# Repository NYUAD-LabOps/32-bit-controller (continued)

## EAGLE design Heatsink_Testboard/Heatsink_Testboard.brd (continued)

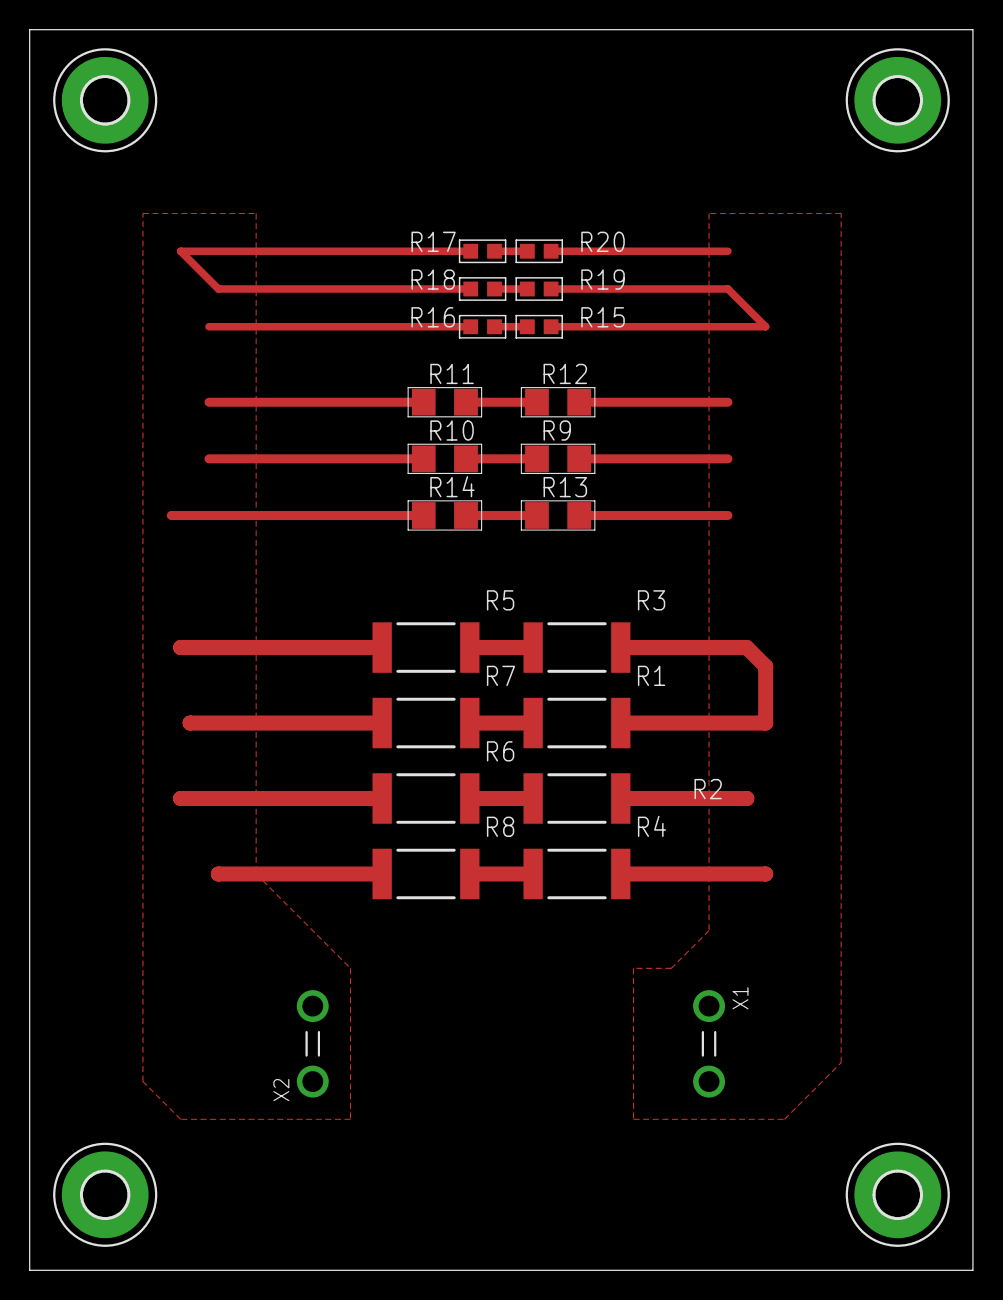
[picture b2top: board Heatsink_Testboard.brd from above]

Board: 2 copper layers, 63.5 x 83.5 mm, 26 parts (0 on the bottom side), 12 nets.

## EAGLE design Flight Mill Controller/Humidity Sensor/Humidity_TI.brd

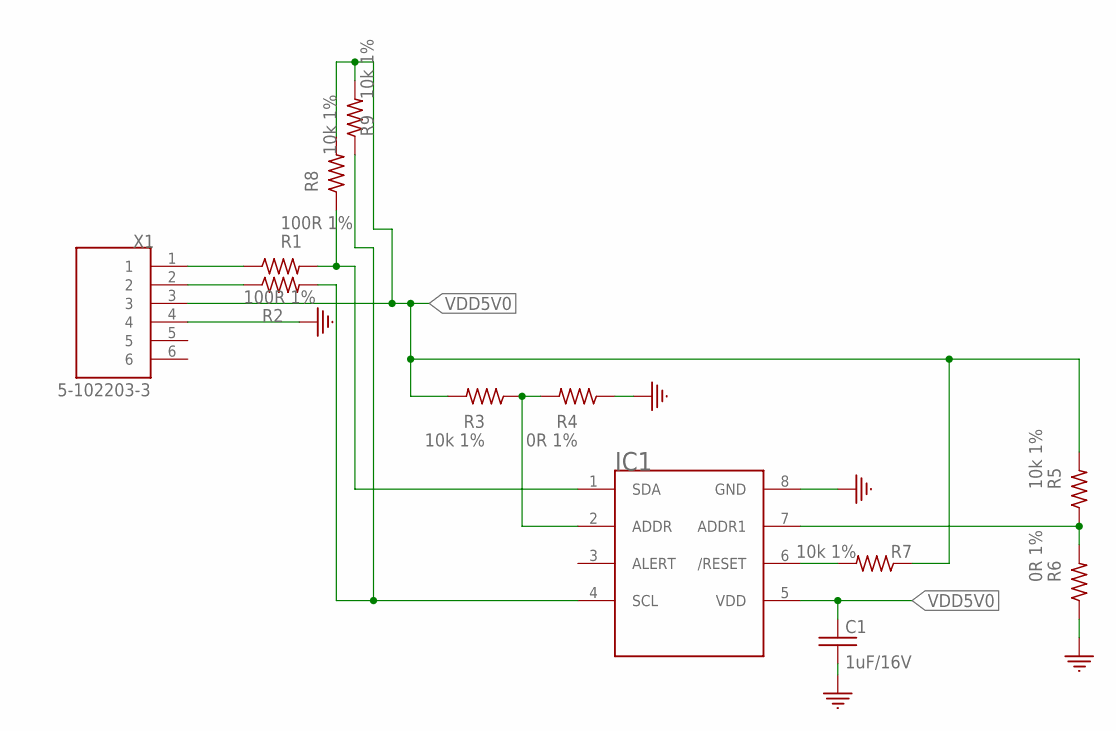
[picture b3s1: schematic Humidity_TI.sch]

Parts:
C1: 1uF/16V; EIA0603
IC1: HDC3021-Q1; WSON8
R1, R2: 100R 1%; EIA0603
R3, R5, R7, R8, R9: 10k 1%; EIA0603
R4, R6: 0R 1%; EIA0603
X1: 5-102203-3; TE_5-102203-3

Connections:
GND: C1.2, IC1.8 (GND), R4.1, R6.1, X1.4
unnamed: R1.1, X1.1
unnamed: IC1.1 (SDA), R1.2, R8.1
unnamed: IC1.4 (SCL), R2.2, R9.1
unnamed: R2.1, X1.2
unnamed: IC1.2 (ADDR), R3.1, R4.2
unnamed: IC1.7 (ADDR1), R5.1, R6.2
unnamed: IC1.6 (/RESET), R7.2
VDD5V0: C1.1, IC1.5 (VDD), R3.2, R5.2, R7.1, R8.2, R9.2, X1.3

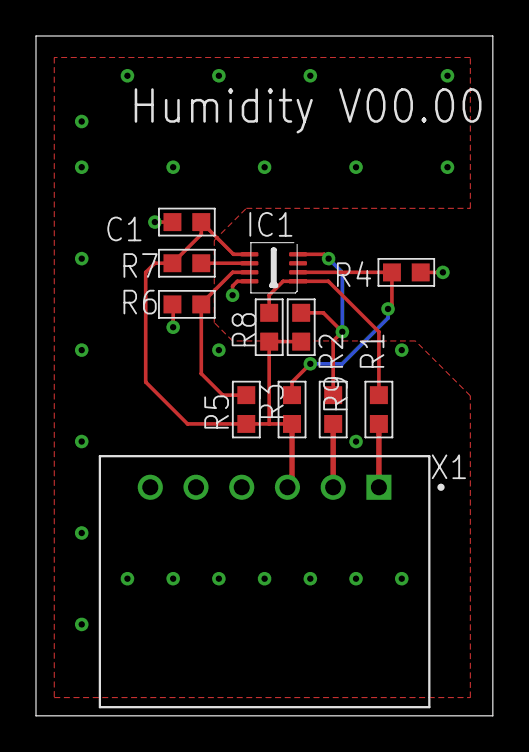
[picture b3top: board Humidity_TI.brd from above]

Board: 2 copper layers, 25.4 x 37.8 mm, 12 parts (0 on the bottom side), 9 nets.

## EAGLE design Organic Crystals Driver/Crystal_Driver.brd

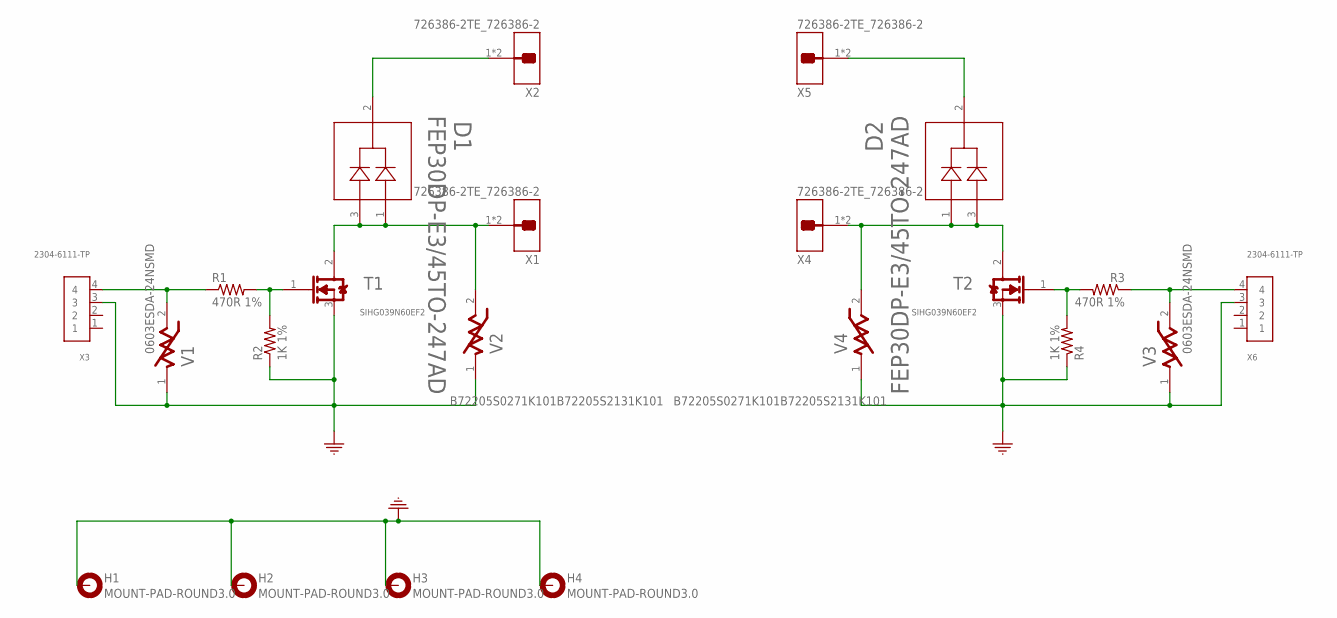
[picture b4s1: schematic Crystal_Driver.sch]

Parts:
D1, D2: FEP30DP-E3/45TO-247AD; TO-247AD
H1, H2, H3, H4: MOUNT-PAD-ROUND3.0; 3,0-PAD
R1, R3: 470R 1%; EIA1206
R2, R4: 1K 1%; EIA0603
T1, T2: SIHG039N60EF2; TO-247AC
V1, V3: 0603ESDA-24NSMD; EIA0603
V2, V4: B72205S0271K101B72205S2131K101; EPCOS_B72205S0271K101_0
X1, X2, X4, X5: 726386-2TE_726386-2; TE_726386-2
X3, X6: 2304-6111-TP; X04_100MIL

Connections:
GND: H1.B3,0, H2.B3,0, H3.B3,0, H4.B3,0, R2.1, R4.1, T1.3 (S), T2.3 (S), V1.1, V2.1, V3.1, V4.1, X3.3, X6.3
unnamed: R1.2, R2.2, T1.1 (G)
unnamed: D1.1, D1.3, T1.2 (D), V2.2, X1.1, X1.1-2
unnamed: D1.2, X2.1, X2.1-2
unnamed: R1.1, V1.2, X3.4
unnamed: R3.2, R4.2, T2.1 (G)
unnamed: D2.1, D2.3, T2.2 (D), V4.2, X4.1, X4.1-2
unnamed: D2.2, X5.1, X5.1-2
unnamed: R3.1, V3.2, X6.4

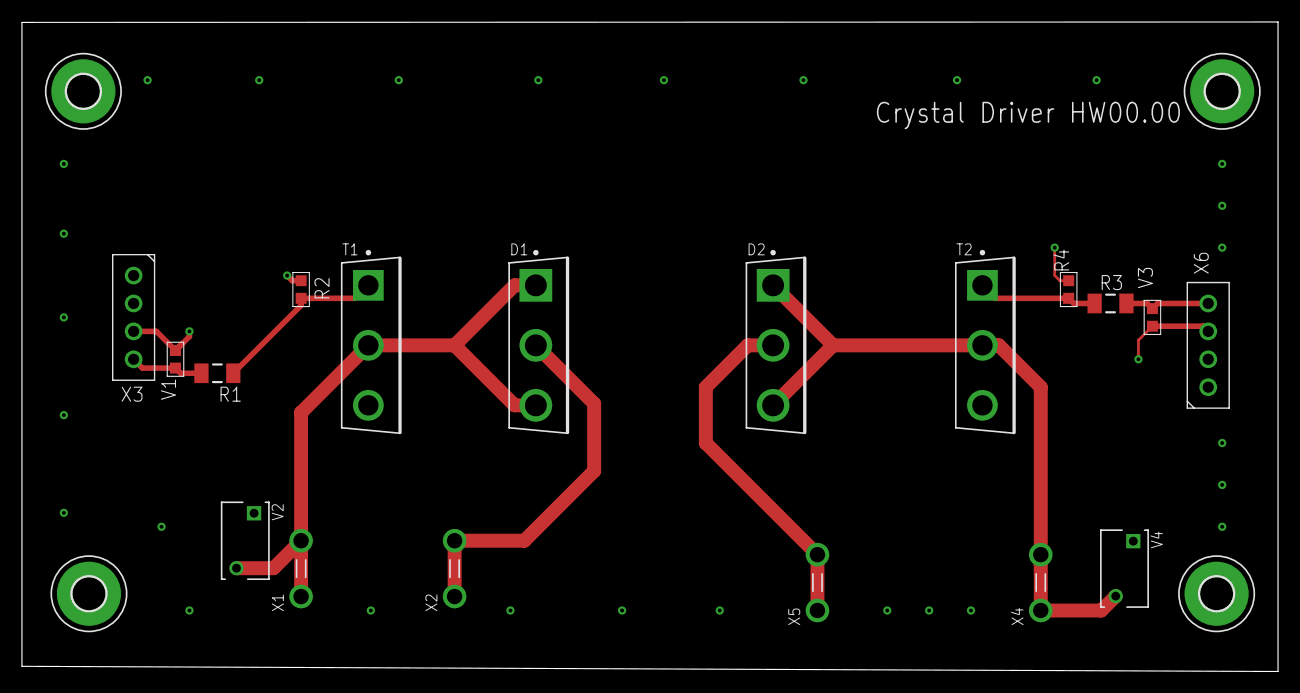
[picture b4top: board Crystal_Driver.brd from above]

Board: 2 copper layers, 114.3 x 59.1 mm, 22 parts (0 on the bottom side), 9 nets.

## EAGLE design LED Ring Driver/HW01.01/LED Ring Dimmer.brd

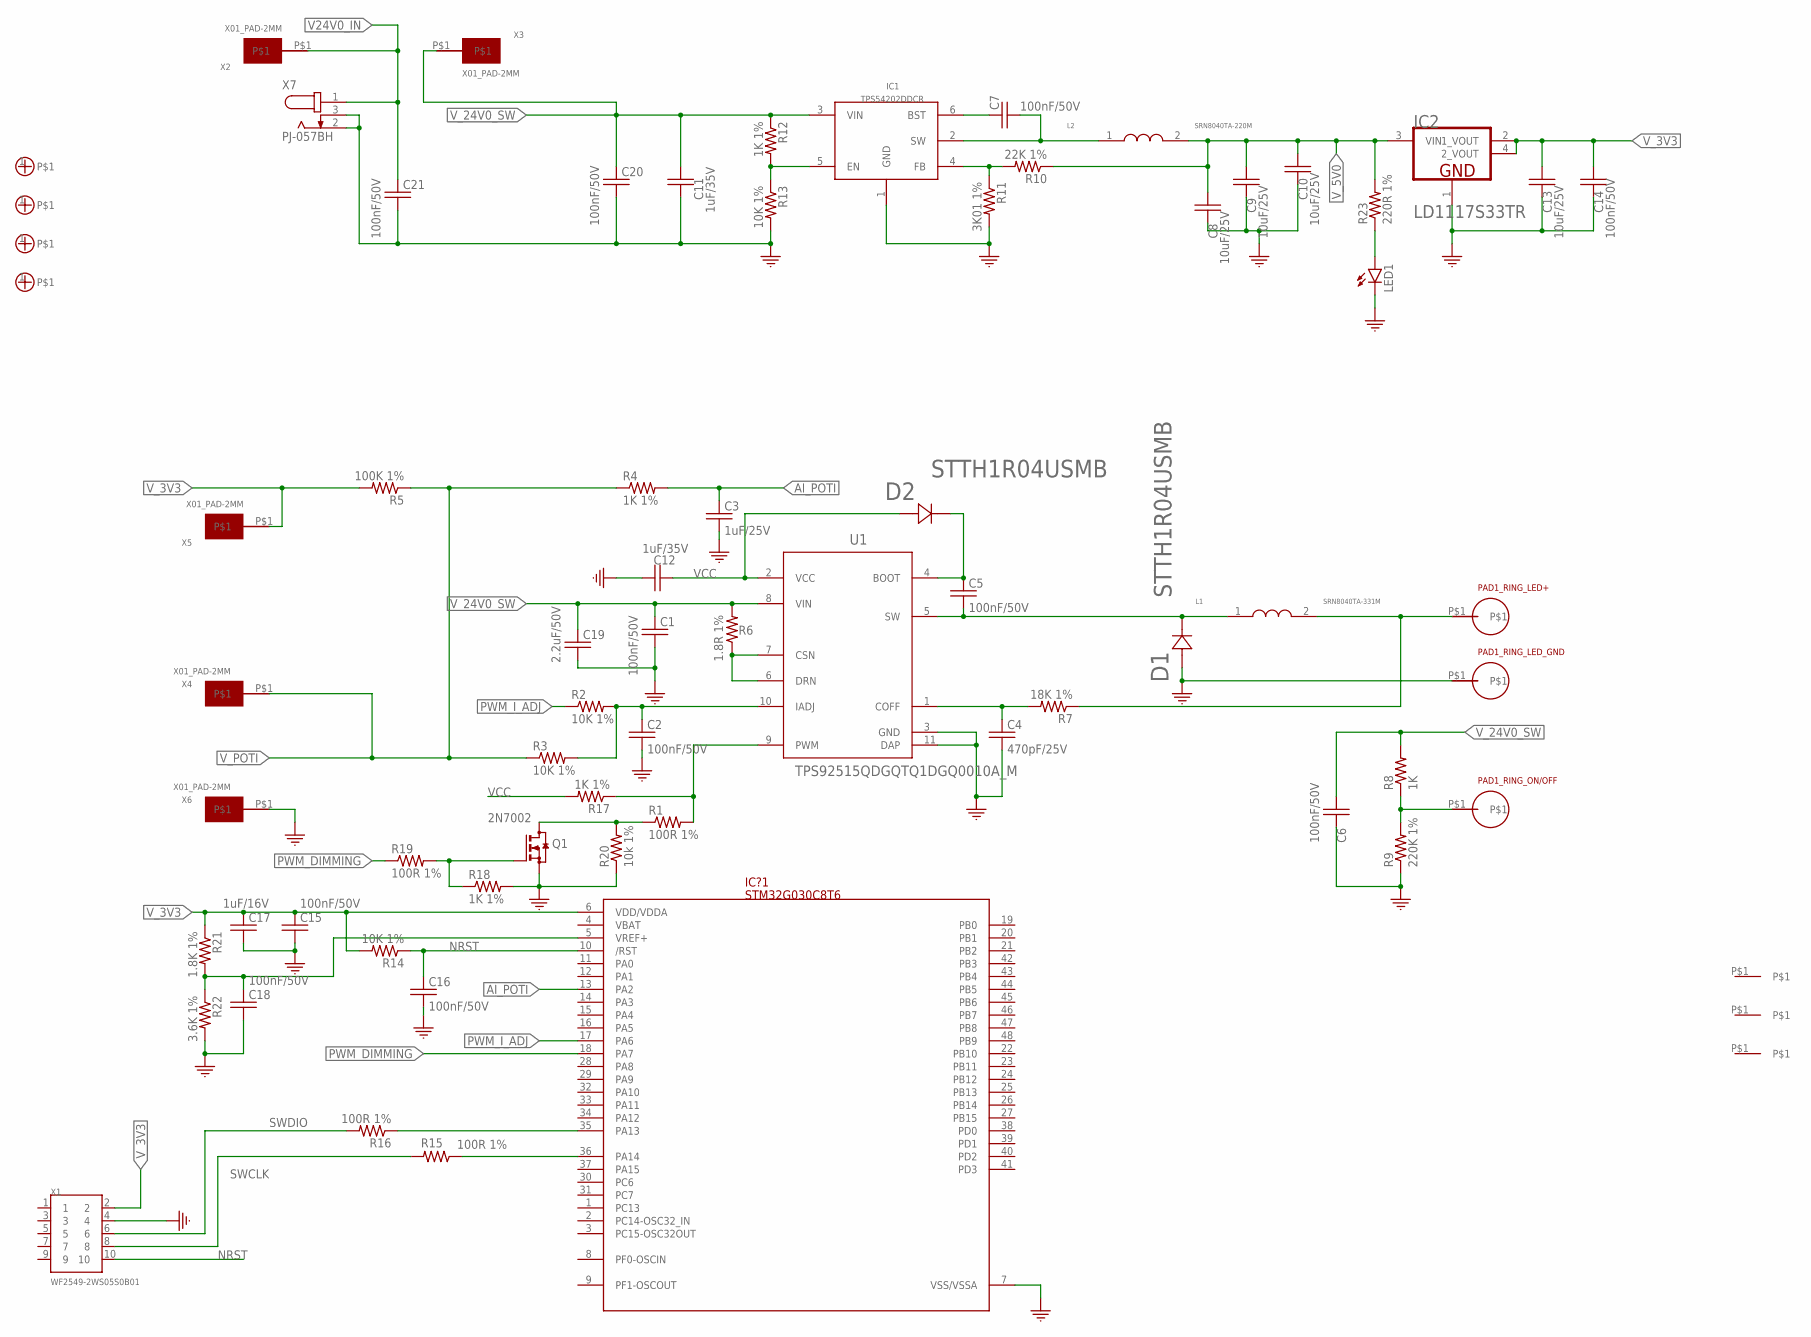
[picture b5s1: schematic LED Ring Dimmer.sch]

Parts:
C1, C2, C5, C6, C7, C14, C15, C16, C18, C20, C21: 100nF/50V; EIA0603
C3: 1uF/25V; EIA0603
C4: 470pF/25V; EIA0603
C8, C9, C10, C13: 10uF/25V; EIA0603
C11, C12: 1uF/35V; EIA0603
C17: 1uF/16V; EIA0603
C19: 2.2uF/50V; EIA0603
D1, D2: STTH1R04USMB; SMB
FID1, FID2, FID3: FIDUCIAL
IC1: TPS54202DDCR; SOT23-6
IC2: LD1117S33TR; SOT223_LD1117S33TR
IC?1: STM32G030C8T6; LQFP48
L1: SRN8040TA-331M; SRN8040TA-220M
L2: SRN8040TA-220M
LED1: LED5MM
M1, M2, M3, M4: M_HOLE_3M; PCB_SCREW_M3_POWER
PAD1_RING_LED+, PAD1_RING_LED_GND, PAD1_RING_ON/OFF: THT_PAD_5MM; THT_PAD_D5.0
Q1: 2N7002; SOT23
R1, R15, R16, R19: 100R 1%; EIA0603
R2, R3, R13, R14: 10K 1%; EIA0603
R4, R12, R17, R18: 1K 1%; EIA0603
R5: 100K 1%; EIA0603
R6: 1.8R 1%; EIA1206
R7: 18K 1%; EIA0603
R8: 1K; EIA0603
R9: 220K 1%; EIA0603
R10: 22K 1%; EIA0603
R11: 3K01 1%; EIA0603
R20: 10k 1%; EIA0603
R21: 1.8K 1%; EIA0603
R22: 3.6K 1%; EIA0603
R23: 220R 1%; EIA1206
U1: TPS92515QDGQTQ1DGQ0010A_M; DGQ0010A_M
X1: WF2549-2WS05S0B01; X10_100MIL_2XROW_VERT
X2, X3, X4, X5, X6: X01_PAD-2MM
X7: PJ-057BH; CUI_PJ-057BH

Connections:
AI_POTI: C3.1, IC?1.13 (PA2), R4.2
GND: C1.2, C2.2, C3.2, C4.2, C6.2, C8.2, C9.2, C10.2, C11.2, C12.1, C13.2, C14.2, C15.2, C16.2, C17.2, C18.2, C19.2, C20.2, C21.2, D1.A, IC1.1 (GND), IC2.1 (GND), IC?1.7 (VSS/VSSA), LED1.K (C), PAD1_RING_LED_GND.P$1, Q1.2 (S), R9.1, R11.2, R13.2, R18.2, R20.1, R22.2, U1.3 (GND), U1.11 (DAP), X1.4, X6.P$1, X7.2, X7.3
unnamed: LED1.A, R23.1
unnamed: C5.2, D1.K (C), L1.1, U1.5 (SW)
unnamed: R6.1, U1.6 (DRN), U1.7 (CSN)
unnamed: C2.1, R2.2, R3.2, U1.10 (IADJ)
unnamed: C4.1, R7.2, U1.1 (COFF)
unnamed: R1.2, R17.1, U1.9 (PWM)
unnamed: L1.2, PAD1_RING_LED+.P$1, R7.1
unnamed: C5.1, D2.K (C), U1.4 (BOOT)
unnamed: PAD1_RING_ON/OFF.P$1, R8.1, R9.2
unnamed: C7.1, IC1.6 (BST)
unnamed: C7.2, IC1.2 (SW), L2.1
unnamed: IC1.4 (FB), R10.2, R11.1
unnamed: Q1.3 (D), R1.1, R20.2
unnamed: IC1.5 (EN), R12.2, R13.1
unnamed: Q1.1 (G), R18.1, R19.2
unnamed: C18.1, IC?1.5 (VREF+), R21.2, R22.1
unnamed: IC?1.35 (PA13), R16.1
unnamed: IC?1.36 (PA14), R15.1
NRST: C16.1, IC?1.10 (/RST), R14.1, X1.10
PWM_DIMMING: IC?1.18 (PA7), R19.1
PWM_I_ADJ: IC?1.17 (PA6), R2.1
SWCLK: R15.2, X1.8
SWDIO: R16.2, X1.6
V24V0_IN: C21.1, X2.P$1, X7.1
VCC: C12.2, D2.A, R17.2, U1.2 (VCC)
V_3V3: C13.1, C14.1, C15.1, C17.1, IC2.2 (1_VOUT), IC2.4 (2_VOUT), IC?1.6 (VDD/VDDA), R5.2, R14.2, R21.1, X1.2, X5.P$1
V_5V0: C8.1, C9.1, C10.1, IC2.3 (VIN), L2.2, R10.1, R23.2
V_24V0_SW: C1.1, C6.1, C11.1, C19.1, C20.1, IC1.3 (VIN), R6.2, R8.2, R12.1, U1.8 (VIN), X3.P$1
V_POTI: R3.1, R4.1, R5.1, X4.P$1

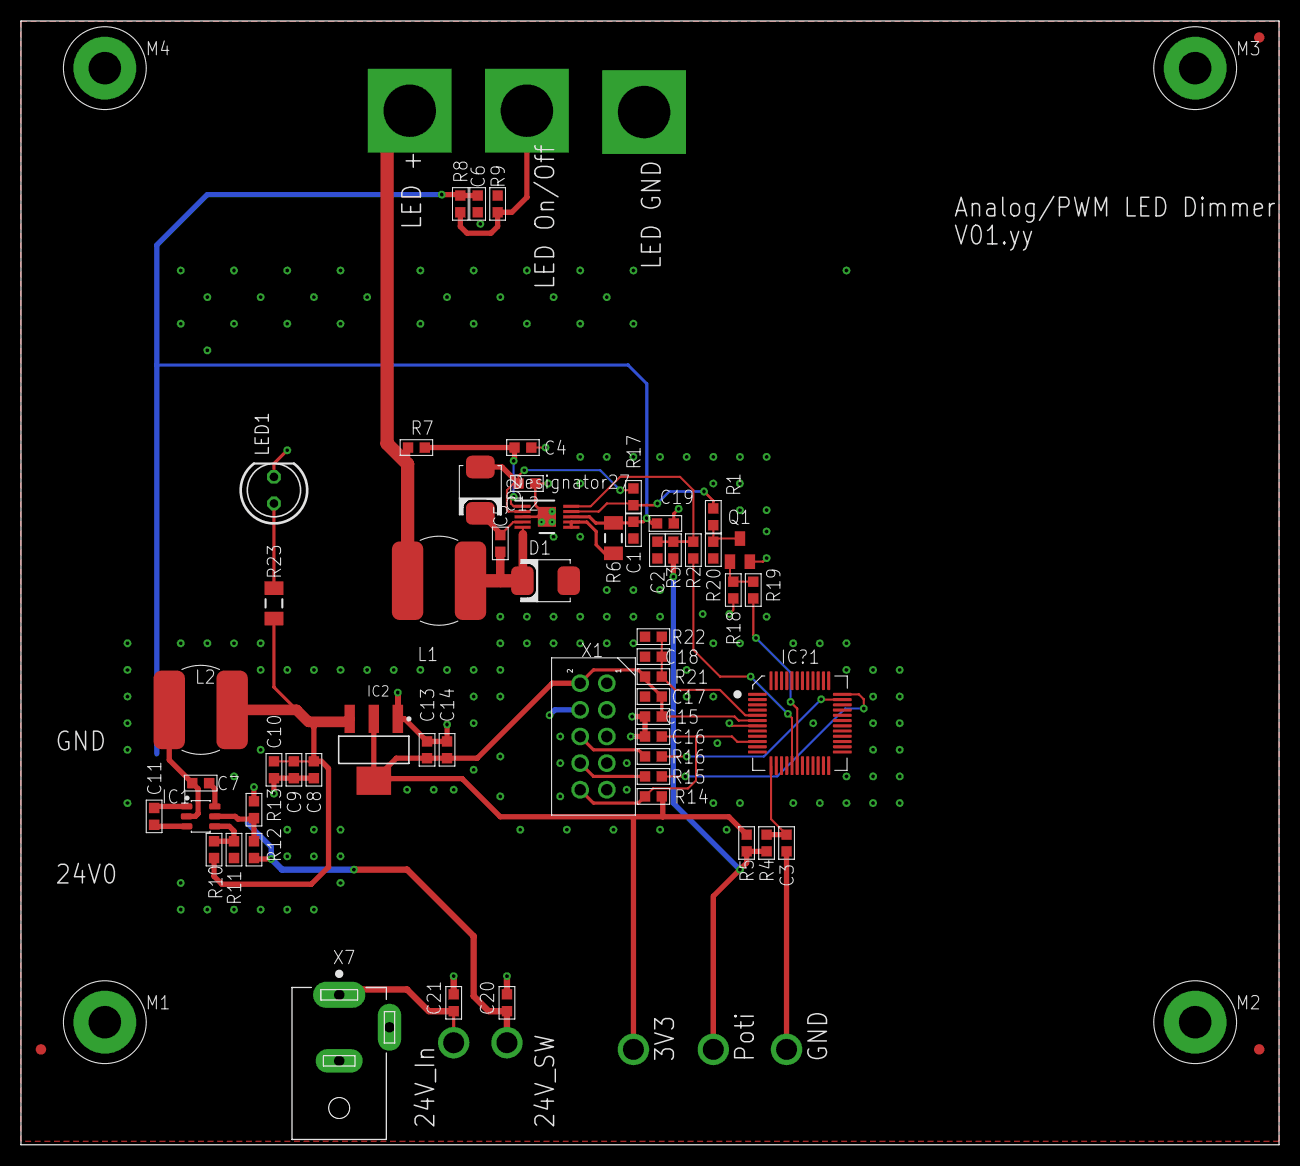
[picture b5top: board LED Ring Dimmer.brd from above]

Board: 2 copper layers, 120.0 x 107.2 mm, 71 parts (0 on the bottom side), 31 nets.

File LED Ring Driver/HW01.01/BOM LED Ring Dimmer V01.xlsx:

Qty | Value | Device | Package | Parts | Description | MFN | MFR | PART_VALUE
11 | 100nF/50V | C_0603EIA0603 | EIA0603 | C1, C2, C5, C6, C7, C14, C15, C16, C18, C20, C21
5 | X01_PAD-2MM | X01_PAD-2MM | X01_PAD-2MM | X2, X3, X4, X5, X6
4 | 100R 1% | R_0603 | EIA0603 | R1, R15, R16, R19 |  | Open Source 0603
4 | 10K 1% | R_0603 | EIA0603 | R2, R3, R13, R14 |  | Open Source 0603
4 | 10uF/25V | C_0603EIA0603 | EIA0603 | C8, C9, C10, C13
4 | 1K 1% | R_0603 | EIA0603 | R4, R12, R17, R18 |  | Open Source 0603
4 | M_HOLE_3M | M_HOLE_3M | PCB_SCREW_M3_POWER | M1, M2, M3, M4
3 | FIDUCIAL | FIDUCIAL | FIDUCIAL | FID1, FID2, FID3
3 | THT_PAD_5MM | THT_PAD_5MM | THT_PAD_D5.0 | PAD1_RING_LED+, PAD1_RING_LED_GND, PAD1_RING_ON/OFF
2 | 1uF/35V | C_0603EIA0603 | EIA0603 | C11, C12
2 | STTH1R04USMB | STTH1R04USMB | SMB | D1, D2 | 1A, 400V, SMB, Fast Recovery | STTH1R04U |  | STTH1R04U
1 |  | LED5MM | LED5MM | LED1 | LED
1 | 1.8K 1% | R_0603 | EIA0603 | R21 |  | Open Source 0603
1 | 1.8R 1% | R_1206EIA1206 | EIA1206 | R6 |  | Open Source R1206
1 | 100K 1% | R_0603 | EIA0603 | R5 |  | Open Source 0603
1 | 10k 1% | R_0603 | EIA0603 | R20 |  | Open Source 0603
1 | 18K 1% | R_0603 | EIA0603 | R7 |  | Open Source 0603
1 | 1K | R_0603 | EIA0603 | R8 |  | Open Source 0603
1 | 1uF/16V | C_0603EIA0603 | EIA0603 | C17
1 | 1uF/25V | C_0603EIA0603 | EIA0603 | C3
1 | 2.2uF/50V | C_0603EIA0603 | EIA0603 | C19
1 | 220K 1% | R_0603 | EIA0603 | R9 |  | Open Source 0603
1 | 220R 1% | R_1206EIA1206 | EIA1206 | R23 |  | Open Source R1206
1 | 22K 1 | R_0603 | EIA0603 | R10 |  | Open Source 0603
1 | 2N7002 | 2N7002 | SOT23 | Q1 | NMOSFET, 500mA, 60V, Vth 2.5V | 2N7002 | Diodes, Guangdong Hotetech,NXP | NMOSFET
1 | 3.6K 1% | R_0603 | EIA0603 | R22 |  | Open Source 0603
1 | 3K01 1% | R_0603 | EIA0603 | R11 |  | Open Source 0603
1 | 470pF/25V | C_0603EIA0603 | EIA0603 | C4
1 | LD1117S33TR | LD1117S33TR | SOT223_LD1117S33TR | IC2 | IC REG LINEAR 3.3V 800mA SOT223 | LD1117S33TR | STmicro, Diodes, TI, | xx1117x33xx
1 | PJ-057BH | PJ-057BH | CUI_PJ-057BH | X7 | DC Power Connectors Power Jack 2.5mm, 2.5A, Male | PJ-057BH | CUI Devices
1 | SRN8040TA-220M | SRN8040TA-220M | SRN8040TA-220M | L2 | FIXED IND 22UH 2.9A SMD, 73m-Ohm, Bourns | SRN8040TA-220M | Bourns | 22uH/2.9A
1 | SRN8040TA-331M | SRN8040TA-331M | SRN8040TA-220M | L1 | FIXED IND 22UH 2.9A SMD, 73m-Ohm, Bourns | SRN8040TA-331M | Bourns | 330uH/0.66A
1 | STM32G030C8T6 | STM32G030C8T6 | LQFP48 | IC?1
1 | TPS54202DDCR | TPS54202DDCR | SOT23-6 | IC1 | 2A 28V SOT-23-6 Sync Buck | TPS54202DDCR | Texas Instruments | TPS54202
1 | TPS92515QDGQTQ1DGQ0010A_M | TPS92515QDGQTQ1DGQ0010A_M | DGQ0010A_M | U1 | LED Driver 2A, 42V, Buck, Analog and PWM Dimming,MSOP-PowerPad-10 | TPS92515QDGQTQ1 | Texas Instruments | TPS92515
1 | WF2549-2WS05S0B01 | WF2549-2WS05S0B01 | X10_100MIL_2XROW_VERT | X1 | X10, 10 Pins, Header, Pitch 2.54 wire to board 2xrows, THT | WF2549-2WS05S0B01 | WCON

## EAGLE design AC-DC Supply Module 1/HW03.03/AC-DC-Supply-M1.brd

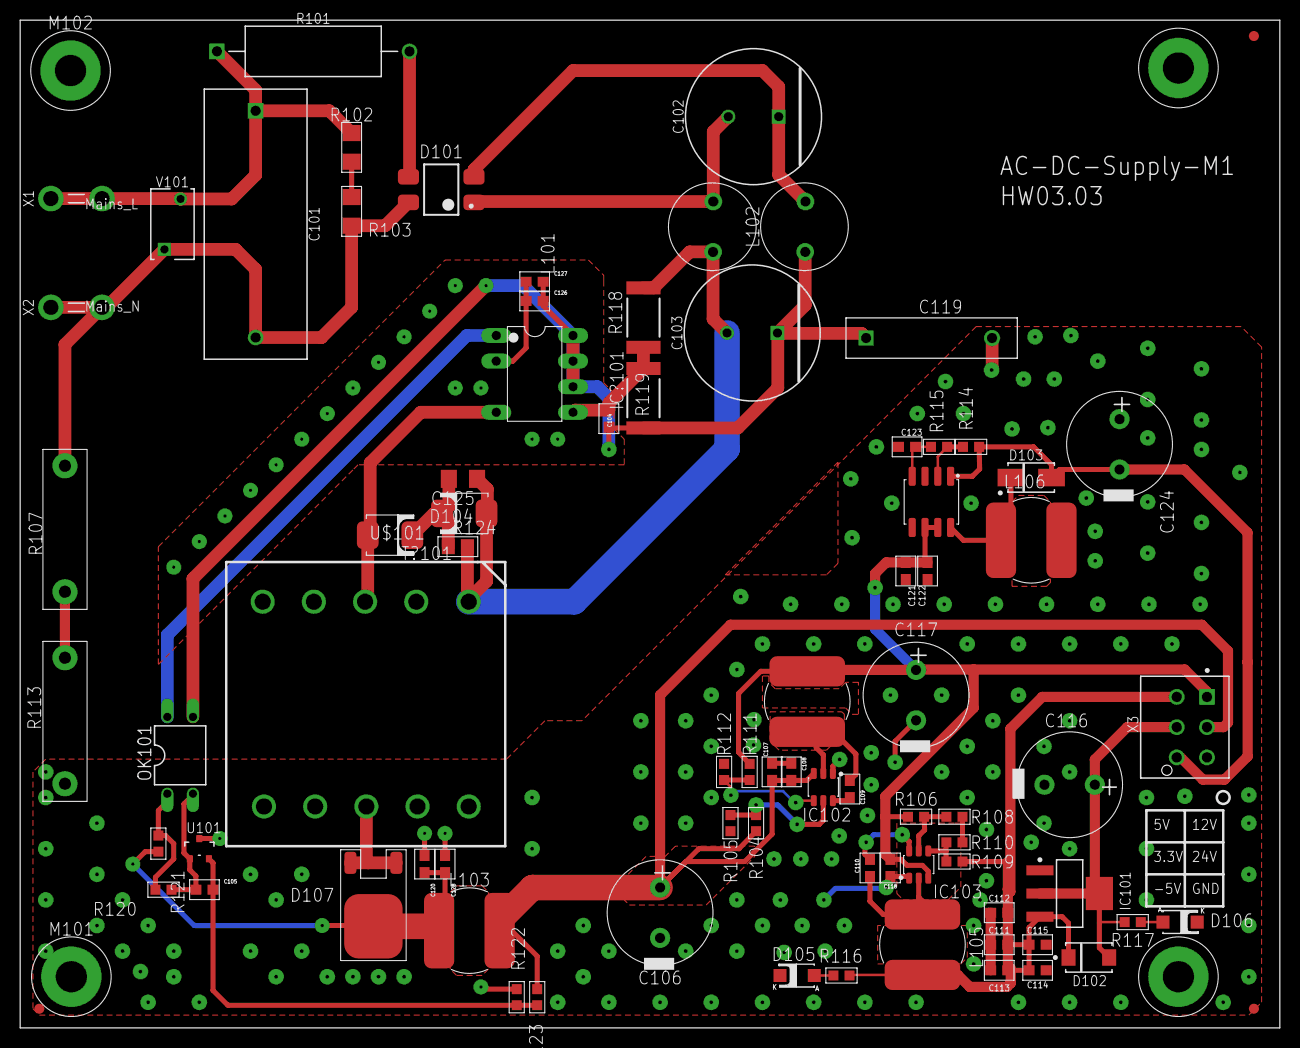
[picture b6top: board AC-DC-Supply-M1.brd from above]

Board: 2 copper layers, 125.0 x 100.0 mm, 85 parts (0 on the bottom side), 38 nets.

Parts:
C101: R49AN347050B1M
C102, C103: 860011378008; RADIAL_D13.0P5.0H25.0
C104, C105, C107, C109, C110, C115, C123, C127: 100nF/50V; 0603
C106, C116, C117, C124: 50PX470MEFC10X20; CAPACITOR-ELKO-RM5-10X16
C108, C118, C120, C121, C128: 1uF/35V; 0603
C111, C112, C113, C114, C122: 10uF/25V; 0603
C119: ERP610W471MEF0; CAP-P12.5-H15-W4-D1
C125: 220pF/1KV; C1206
C126: 1u/35V; 0603
D101: MB10S; SOIC4W
D102: STTH1L06ASTMICROELECTRONICS_STTH1L06A_0_0; SMA_STTH1L06A
D103: SS14; SMA
D104: STTH1R04USMB; SMB
D105, D106: 26-21/GPC-F3138B/CA; SMD1206-LED
D107: STTH1003SB-TR; DPAK
FID101, FID102, FID103: FIDUCIAL
IC101: LD1117S33TR; SOT223_LD1117S33TR
IC102, IC103: TPS54202DDCR; SOT23-6
IC104: MAX764CSA+; SOIC8
IC?101: NCP1079BBP100G; PDIP-8C
L101, L102: RLB0914-102KL; THTINDUCTOR8MM7
L103, L104, L105, L106: SRN8040TA-220M
M101, M102, M103, M104: M_HOLE_3M; PCB_SCREW_M3_POWER
OK101: SFH615; DIL04
R101: ERG-2SJ390V; ERG-2SJ390V_0
R102, R103: R_1206; R1206
R104: 1K 1%; EIA0603
R105: 10K; EIA0603
R106: 1K 1 %; EIA0603
R107, R113: RNF12FTD10M0; RES-RM12.5-VR37
R108, R115: 10k 1%; EIA0603
R109: 22K 1%; EIA0603
R110: 3k01 1%; EIA0603
R111: 100k 1%; EIA0603
R112: 4.3k 1%; EIA0603
R114: 33k 1%; EIA0603
R116: 162R 1%; EIA0603
R117: 82R 1%; EIA0603
R118: 150K 1%; EIA2512
R119: 1K 1%; EIA2512
R120: 4.7K 1%; EIA0603
R121: 100R 1%; EIA0603
R122: 33K 1%; EIA0603
R123: 5.6K 1%; EIA0603
R124: ERA-8AEB124V; R0805
T?101: FLYBACK_TR_NYUAD01; E25-13-7$20$TRANSFORMER
U101: TL431AQDBZR,215NEXPERIA_TL431AQDBZR,215_0_0; SOT23_TL431AQDBZR,215
U$101: P6SMB120AT3GSMB; SMB
V101: B72205S0271K101B72205S2131K101; EPCOS_B72205S0271K101_0
X1, X2: 726386-2; TE_726386-2_MODIFIED
X3: MOLEX_206832-0601MOLEX_206832-0601; MOLEX_206832-0601

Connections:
10_AC-DC_SUPPLY:N$1: IC102.4, R111.2, R112.2
10_AC-DC_SUPPLY:N$2: R102.1, R103.2
10_AC-DC_SUPPLY:N$3: R107.2, R113.1
10_AC-DC_SUPPLY:N$4: D101.3, R101.2
10_AC-DC_SUPPLY:N$5: C102.2, D101.1, L101.1
10_AC-DC_SUPPLY:N$6: C102.1, D101.2, L102.1
10_AC-DC_SUPPLY:N$7: C103.2, C125.1, L101.2, R118.2, R124.2, T?101.1, U$101.A
10_AC-DC_SUPPLY:N$8: C105.2, R122.1, R123.2, U101.2
10_AC-DC_SUPPLY:N$9: C109.2, IC102.2, L104.1
10_AC-DC_SUPPLY:N$10: IC102.5, R104.1, R105.2
10_AC-DC_SUPPLY:N$11: C126.1, C127.1, IC?101.2
10_AC-DC_SUPPLY:N$12: C109.1, IC102.6
10_AC-DC_SUPPLY:N$13: C110.2, IC103.2, L105.1
10_AC-DC_SUPPLY:N$14: IC104.2, R114.1, R115.2
10_AC-DC_SUPPLY:N$15: IC103.4, R109.2, R110.1
10_AC-DC_SUPPLY:N$16: IC103.5, R106.1, R108.2
10_AC-DC_SUPPLY:N$17: D105.1, R116.2
10_AC-DC_SUPPLY:N$18: D103.1, IC104.8, L106.2
10_AC-DC_SUPPLY:N$19: D106.1, R117.2
10_AC-DC_SUPPLY:N$20: C123.1, IC104.4, R115.1
10_AC-DC_SUPPLY:N$21: C110.1, IC103.6
10_AC-DC_SUPPLY:N$22: D104.A, IC?101.4, T?101.3
10_AC-DC_SUPPLY:N$23: D107.1, D107.3, T?101.8
10_AC-DC_SUPPLY:N$24: C120.2, C128.2, D107.2, L103.1, R121.2
10_AC-DC_SUPPLY:N$25: C104.1, IC?101.5, R118.1, R119.2
10_AC-DC_SUPPLY:N$26: IC?101.1, OK101.4
10_AC-DC_SUPPLY:N$27: C105.1, OK101.2, R120.1, U101.1
10_AC-DC_SUPPLY:N$28: OK101.1, R120.2, R121.1
10_AC-DC_SUPPLY:N$29: C125.2, D104.K, R124.1, U$101.K
10_AC-DC_SUPPLY:V_RECT_F_MINUS: C103.1, C104.2, C119.P$1, C126.2, C127.2, IC?101.6, IC?101.7, IC?101.8, L102.2, OK101.3, R119.1
GND: C106.2, C107.2, C108.2, C111.1, C112.1, C113.1, C114.1, C115.2, C116.2, C117.2, C118.1, C119.P$2, C120.1, C121.1, C122.1, C123.2, C124.1, C128.1, D105.2, D106.2, IC101.1, IC102.1, IC103.1, IC104.3, IC104.5, L106.1, M101.1, M104.1, R105.1, R108.1, R110.2, R112.1, R113.2, R123.1, T?101.6, U101.3, X3.5
unnamed: C101.1, R101.1, R102.2, V101.2, X1.1, X1.1-2
unnamed: C101.2, D101.4, R103.1, R107.1, V101.1, X2.1, X2.1-2
V_3V3: C116.1, D102.2, IC101.2, IC101.4, R117.1, X3.4
V_5V0: C111.2, C112.2, C113.2, C114.2, C115.1, D102.1, IC101.3, L105.2, R109.1, R116.1, X3.2
V_12V0: C117.1, C118.2, C121.2, C122.2, IC103.3, IC104.6, IC104.7, L104.2, R106.2, R111.1, X3.1
V_24V0: C106.1, C107.1, C108.1, IC102.3, L103.2, R104.2, R122.2, X3.3
V_-5V0: C124.2, D103.2, IC104.1, R114.2, X3.6

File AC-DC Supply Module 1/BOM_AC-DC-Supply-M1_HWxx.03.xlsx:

Part | Value | Device | Package | DESCRIPTION.1 | LIB_STATUS | MF | MFN | MFR | MPN | OUR_STOCK | PART_VALUE | PRICE-1 | SUPPLIER-1
C101 | R49AN347050B1M | R49AN347050B1M | R49AN347050B1M | Film,X1,470nF/330Vac,THT | Verified |  | R49AN347050B1M | Kemet |  | 8 | 470nF/330VAC | 1.51 | Digikey
C102 | 860011378008 | 860011378008 | RADIAL_D13.0P5.0H25.0 | Electrolytic Cap 33ÂµF 400V 13mm Radial WCAP-ATG8 |  |  |  | 860011378008
C103 | 860011378008 | 860011378008 | RADIAL_D13.0P5.0H25.0 | Electrolytic Cap 33ÂµF 400V 13mm Radial WCAP-ATG8 |  |  |  | 860011378008
C104 | 50PX470MEFC10X20 | 50PX470MEFC10X20 | CAPACITOR-ELKO-RM5-10X16 | 470uF Â±20% 50V 10mm 20mm 5mm 2000Hrs @ 105â„ƒ -55â„ƒ ~ +105â„ƒ | Prototype |  | 50PX470MEFC10X20 | Rubicon |  | 20 | 470uF/50V | 0.14000000000000001 | LCSC
C105 | 50PX470MEFC10X20 | 50PX470MEFC10X20 | CAPACITOR-ELKO-RM5-10X16 | 470uF Â±20% 50V 10mm 20mm 5mm 2000Hrs @ 105â„ƒ -55â„ƒ ~ +105â„ƒ | Prototype |  | 50PX470MEFC10X20 | Rubicon |  | 20 | 470uF/50V | 0.14000000000000001 | LCSC
C106 | 50PX470MEFC10X20 | 50PX470MEFC10X20 | CAPACITOR-ELKO-RM5-10X16 | 470uF Â±20% 50V 10mm 20mm 5mm 2000Hrs @ 105â„ƒ -55â„ƒ ~ +105â„ƒ | Prototype |  | 50PX470MEFC10X20 | Rubicon |  | 20 | 470uF/50V | 0.14000000000000001 | LCSC
C107 | 100nF/50V | C_0603 | 0603 |  |  |  | Open Source
C108 | 1uF/35V | C_0603 | 0603 |  |  |  | Open Source
C109 | 100nF/50V | C_0603 | 0603 |  |  |  | Open Source
C110 | 100nF/50V | C_0603 | 0603 |  |  |  | Open Source
C111 | 10uF/25V | C_0603 | 0603 |  |  |  | Open Source
C112 | 10uF/25V | C_0603 | 0603 |  |  |  | Open Source
C113 | 10uF/25V | C_0603 | 0603 |  |  |  | Open Source
C114 | 10uF/25V | C_0603 | 0603 |  |  |  | Open Source
C115 | 100nF/50V | C_0603 | 0603 |  |  |  | Open Source
C116 | 50PX470MEFC10X20 | 50PX470MEFC10X20 | CAPACITOR-ELKO-RM5-10X16 | 470uF Â±20% 50V 10mm 20mm 5mm 2000Hrs @ 105â„ƒ -55â„ƒ ~ +105â„ƒ | Prototype |  | 50PX470MEFC10X20 | Rubicon |  | 20 | 470uF/50V | 0.14000000000000001 | LCSC
C117 | 50PX470MEFC10X20 | 50PX470MEFC10X20 | CAPACITOR-ELKO-RM5-10X16 | 470uF Â±20% 50V 10mm 20mm 5mm 2000Hrs @ 105â„ƒ -55â„ƒ ~ +105â„ƒ | Prototype |  | 50PX470MEFC10X20 | Rubicon |  | 20 | 470uF/50V | 0.14000000000000001 | LCSC
C118 | 1uF/35V | C_0603 | 0603 |  |  |  | Open Source
C119 | ERP610W471MEF0 | ERP610W471MEF0 | CAP-P12.5-H15-W4-D1 | 470 pF Â±20% 760VAC Ceramic Capacitor Y5U (E) Radial X1,Y1 | Prototype |  | ERP610W471MEF0 | Kemet |  | 150 | 470pF/760VAC | 0.42 | Digikey
C120 | ERP610W471MEF0 | ERP610W471MEF0 | CAP-P12.5-H15-W4-D1 | 470 pF Â±20% 760VAC Ceramic Capacitor Y5U (E) Radial X1,Y1 | Prototype |  | ERP610W471MEF0 | Kemet |  | 150 | 470pF/760VAC | 0.42 | Digikey
C121 | 1uF/35V | C_0603 | 0603 |  |  |  | Open Source
C122 | 10uF/25V | C_0603 | 0603 |  |  |  | Open Source
C123 | 100nF/50V | C_0603 | 0603 |  |  |  | Open Source
C124 | 50PX470MEFC10X20 | 50PX470MEFC10X20 | CAPACITOR-ELKO-RM5-10X16 | 470uF Â±20% 50V 10mm 20mm 5mm 2000Hrs @ 105â„ƒ -55â„ƒ ~ +105â„ƒ | Prototype |  | 50PX470MEFC10X20 | Rubicon |  | 20 | 470uF/50V | 0.14000000000000001 | LCSC
D101 | MB10S | MB10S | SOIC4W | 0.5 A 1000 V Low Leakage SMT Bridge Rectifier - SOIC-4 | Prototype |  | MB10S | On Semi, Diodes,MDD |  |  | Bridge Rectifier | 0.02 | Digikey
c | STTH1L06ASTMICROELECTRONICS_STTH1L06A_0_0 | STTH1L06ASTMICROELECTRONICS_STTH1L06A_0_0 | SMA_STTH1L06A |  |  | STMicroelectronics | STTH1L06A
D103 | SS14 | SS14 | SMA | Diode Schottky 1A/40V (SMA) | Prototype |  | SS14-LTP | MCC |  | 10 | Schottky 1A/40V | 0.05 | LCSC
D105 | 26-21/GPC-F3138B/CA | 26-21/GPC-F3138B/CA | SMD1206-LED | Green SMD LED 1206, 160mcd | Prototype |  | 26-21/GPC-F3138B/CA | Everlight |  | 50 | Green LED | 0.06 | LCSC
D106 | 26-21/GPC-F3138B/CA | 26-21/GPC-F3138B/CA | SMD1206-LED | Green SMD LED 1206, 160mcd | Prototype |  | 26-21/GPC-F3138B/CA | Everlight |  | 50 | Green LED | 0.06 | LCSC
FID101 | FIDUCIAL | FIDUCIAL | FIDUCIAL
FID102 | FIDUCIAL | FIDUCIAL | FIDUCIAL
IC101 | LD1117S33TR | LD1117S33TR | SOT223_LD1117S33TR | LDO,Fixed 15V 3.3V 1.3V @ 800mA SOT-223 | Verified |  | LD1117S33TR | STmicro, Diodes, TI, |  | 10 | xx1117x33xx | 7.0000000000000007E-2 | LCSC
IC102 | TPS54202DDCR | TPS54202DDCR | SOT23-6 | 2A 28V SOT-23-6 Sync Buck | Prototype |  | TPS54202DDCR | Texas Instruments |  | 40 | TPS54202 | 1.8 | LCSC
IC103 | TPS54202DDCR | TPS54202DDCR | SOT23-6 | 2A 28V SOT-23-6 Sync Buck | Prototype |  | TPS54202DDCR | Texas Instruments |  | 40 | TPS54202 | 1.8 | LCSC
IC104 | MAX764CSA+ | MAX764CSA+ | SOIC8 |  |  |  | MAX764CSA+ | Max IC |  | 30 | Buck/Boost IC | 4 | Mouser
L101 | RLB0914-102KL | RLB0914-102KL | THTINDUCTOR8MM7 | Inductor Power Wirewound 1mH 10% 252KHz 40Q-Factor Ferrite 300mA 2.1Ohm | Prototype |  | RLB0914-102KL | Bourns |  | 0 | 1mH | 0.42 | Digikey
L102 | RLB0914-102KL | RLB0914-102KL | THTINDUCTOR8MM7 | Inductor Power Wirewound 1mH 10% 252KHz 40Q-Factor Ferrite 300mA 2.1Ohm | Prototype |  | RLB0914-102KL | Bourns |  | 0 | 1mH | 0.42 | Digikey
L103 | SRN8040TA-220M | SRN8040TA-220M | SRN8040TA-220M | FIXED IND 22UH 2.9A SMD, 73m-Ohm, Bourns | Verified |  | SRN8040TA-220M | Bourns |  | 10 | 22uH/2.9A |  | Digikey
L104 | SRN8040TA-220M | SRN8040TA-220M | SRN8040TA-220M | FIXED IND 22UH 2.9A SMD, 73m-Ohm, Bourns | Verified |  | SRN8040TA-220M | Bourns |  | 10 | 22uH/2.9A |  | Digikey
L105 | SRN8040TA-220M | SRN8040TA-220M | SRN8040TA-220M | FIXED IND 22UH 2.9A SMD, 73m-Ohm, Bourns | Verified |  | SRN8040TA-220M | Bourns |  | 10 | 22uH/2.9A |  | Digikey
L106 | SRN8040TA-220M | SRN8040TA-220M | SRN8040TA-220M | FIXED IND 22UH 2.9A SMD, 73m-Ohm, Bourns | Verified |  | SRN8040TA-220M | Bourns |  | 10 | 22uH/2.9A |  | Digikey
R101 | ERG-2SJ390V | ERG-2SJ390V | ERG-2SJ390V_0 |  | Verified
R102 | R_1206 | R_1206 | R1206 |  | Verified |  | CRCW1206220KJNEAHP | Vishay |  |  | 220K 5%
R103 | R_1206 | R_1206 | R1206 |  | Verified |  | CRCW1206220KJNEAHP | Vishay |  |  | 220K 5%
R104 | 1K 1% | R_0603 | R0603 |  |  |  | Open Source
R105 | 10K | R_0603 | R0603 |  |  |  | Open Source
R106 | 1K 1 % | R_0603 | R0603 |  |  |  | Open Source
R107 | RNF12FTD10M0 | RNF12FTD10M0 | RES-RM12.5-VR37 | 10 MOhms Â±1% 0.5W, 1/2W Through Hole Resistor Axial Flame Retardant Coating, S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 | Prototype |  | RNF12FTD10M0 | Stackpole Electronics Inc |  |  | 10Meg 5% | 0.28999999999999998 | Digikey
R108 | 10k 1% | R_0603 | R0603 |  |  |  | Open Source
R109 | 15.8K 1% | R_0603 | R0603 |  |  |  | Open Source
R110 | 3k01 1% | R_0603 | R0603 |  |  |  | Open Source
R111 | 47k 1% | R_0603 | R0603 |  |  |  | Open Source
R112 | 3.3k 1% | R_0603 | R0603 |  |  |  | Open Source
R113 | RNF12FTD10M0 | RNF12FTD10M0 | RES-RM12.5-VR37 | 10 MOhms Â±1% 0.5W, 1/2W Through Hole Resistor Axial Flame Retardant Coating, S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 | Prototype |  | RNF12FTD10M0 | Stackpole Electronics Inc |  |  | 10Meg 5% | 0.28999999999999998 | Digikey
R114 | 10k 1% | R_0603 | R0603 |  |  |  | Open Source
R115 | 10k 1% | R_0603 | R0603 |  |  |  | Open Source
R116 | 162R 1% | R_0603 | R0603 |  |  |  | Open Source
R117 | 82R 1% | R_0603 | R0603 |  |  |  | Open Source
U101 | BPM2417SJ | BPM2417SJ | BPM2417SJ | Ac/Dc Power Supply Module | Prototype |  | BPM2417SJ | Tamura |  | 5 | Power Sources | 7 | Digikey
V101 | B72205S0271K101B72205S2131K101 | B72205S0271K101B72205S2131K101 | EPCOS_B72205S0271K101_0 |  | Verified |  | B72205S0271K1011 | EPCOS |  | 10 | 430V, 400A | 0.31 | Digikey
X1 | 726386-2 | 726386-2 | TE_726386-2_MODIFIED | 0.250 (6.35mm) Quick Connect Male - Solder Connector Non-Insulated" |  |  | 726386-2 | TE Connectivity |  |  | 6.35mmx8mm | 0.24 | Digikey
X2 | 726386-2 | 726386-2 | TE_726386-2_MODIFIED | 0.250 (6.35mm) Quick Connect Male - Solder Connector Non-Insulated" |  |  | 726386-2 | TE Connectivity |  |  | 6.35mmx8mm | 0.24 | Digikey
X3 | MOLEX_206832-0601MOLEX_206832-0601 | MOLEX_206832-0601MOLEX_206832-0601 | MOLEX_206832-0601 | Connector Header Through Hole 6 position 3mm Microfit | Prototype |  | 206832-0601 | Molex |  | 20 | 6CCT x 2Row | 1.32 | Digikey
